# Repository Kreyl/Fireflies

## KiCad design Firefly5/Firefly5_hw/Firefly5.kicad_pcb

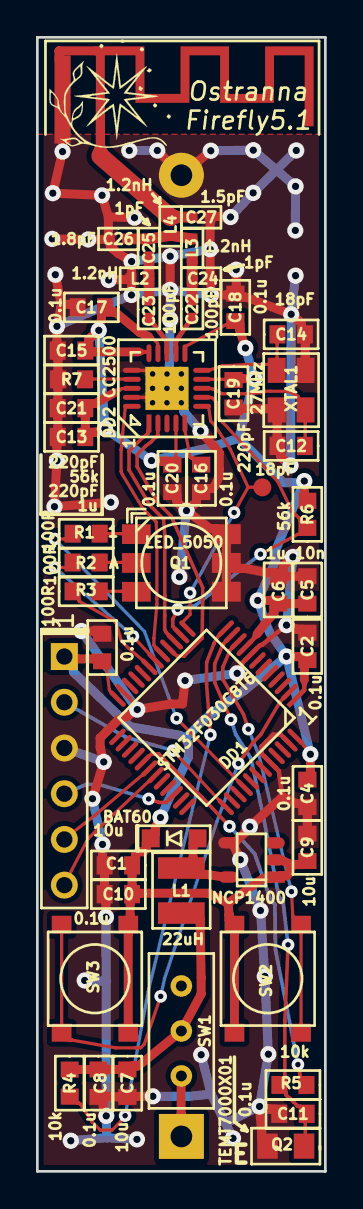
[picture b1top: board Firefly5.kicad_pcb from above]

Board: 2 copper layers, 16.0 x 63.0 mm, 53 parts (1 on the bottom side), 35 nets.

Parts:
ANT1: ANT_GENERAL; ANT_2400_MEANDER_MIRR
B1: BAT; BATTERY_AA
C1, C7, C9: 10u; CAP_0603
C2, C3, C4, C8, C10, C11, C16, C17, C18, C20: 0.1u; CAP_0603
C5: 10n; CAP_0603
C6, C13: 1u; CAP_0603
C12, C14: 18pF; CAP_0603
C15, C19, C21: 220pF; CAP_0603
C22, C23: 100pF; CAP_0402
C24, C25: 1pF; CAP_0402
C26: 1.8pF; CAP_0402
C27: 1.5pF; CAP_0402
D1: BAT60; SOD323
DA1: NCP1400; SOT23-5
DD1: STM32F030C8T6; LQFP48
DD2: CC2500; QFN20
L1: 22uH; IND_1210_LQH32C
L2, L3, L4: 1.2nH; IND_0402
Logo1: Logo; Ostranna_8x8
Q1: LED_5050
Q2: TEMT7000X01; RES_0805
R1, R2, R3: 100R; RES_0603
R4, R5: 10k; RES_0603
R6, R7: 56k; RES_0603
SW1: SWITCH; SW_SS-1P2T
SW2, SW3: Btn4x4; BTN_4x4_SMD
TP1: TESTPOINT; TESTPOINT_1MM
XL1: CONN_6; PLS-6
XTAL1: 27MHz; 03225C4

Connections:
+3.3V: C1.1, C2.1, C3.1, C4.1, C5.1, C6.1, C9.1, C10.1, C13.1, C15.1, C17.1, C18.1, C19.1, C20.1, C21.1, D1.C, DA1.1, DA1.2, DD1.1, DD1.9, DD1.24, DD1.48, DD2.4, DD2.9, DD2.11, DD2.14, DD2.15, DD2.18, R6.2, SW2.1, SW3.1, XL1.1
+BATT: C7.1, C8.1, L1.2, R4.1, SW1.2
/BAT_IN: B1.A, SW1.1
/BLUE_LED: DD1.40, R1.1
/BTN1: DD1.10, SW2.2
/BTN2: DD1.2, SW3.2
/CC_CS: DD1.14, DD2.7, R6.1
/CC_GDO0: DD1.13, DD2.6, TP1.1
/CC_MISO: DD1.16, DD2.2
/CC_MOSI: DD1.17, DD2.20
/CC_SCK: DD1.15, DD2.1
/GREEN_LED: DD1.19, R3.1
/LUM_MEAS: C11.1, DD1.11, Q2.1, R5.2
/Lout: D1.A, DA1.5, L1.1
/RED_LED: DD1.18, R2.1
/SWCLK: DD1.37, XL1.2
/SWDIO: DD1.34, XL1.4
/UART_RX: DD1.31, XL1.6
/UART_TX: DD1.30, XL1.5
GND: ANT1.2, B1.C, C1.2, C2.2, C3.2, C4.2, C5.2, C6.2, C7.2, C8.2, C9.2, C10.2, C11.2, C12.2, C13.2, C14.2, C15.2, C16.1, C17.2, C18.2, C19.2, C20.2, C21.2, C24.1, C26.1, C27.1, DA1.4, DD1.8, DD1.23, DD1.44, DD1.47, DD2.16, DD2.19, DD2.PAD, L2.2, Q1.4, Q1.5, Q1.6, Q2.2, R7.2, XL1.3, XTAL1.H
unnamed: ANT1.1, C27.2, L4.1
unnamed: C12.1, DD2.8, XTAL1.1
unnamed: C14.1, DD2.10, XTAL1.2
unnamed: C16.2, DD2.5
unnamed: C22.1, DD2.12
unnamed: C22.2, C24.2, L3.2
unnamed: C23.1, DD2.13
unnamed: C23.2, C25.1, L2.1
unnamed: C25.2, C26.2, L3.1, L4.2
unnamed: DD1.12, R4.2
unnamed: DD1.29, R5.1
unnamed: DD2.17, R7.1
unnamed: Q1.1, R1.2
unnamed: Q1.2, R2.2
unnamed: Q1.3, R3.2

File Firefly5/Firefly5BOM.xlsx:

Reference | Value | Footprint | Quantity | PN | SolderPointsDIP | Price | SolderPoints | URL | Sum
ANT1 | ANT_GENERAL | Radio:ANT_2400_MEANDER_MIRR | 1
B1 | BAT | Installation:BATTERY_AA | 1
C1 C7 C9 | 10u | Capacitors:CAP_0603 | 3 | CL10A106MQ8NNNC |  | 2.5 | 2 | https://www.terraelectronica.ru/catalog.php?ID=1155&search=c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
C12 C14 | 18pF | Capacitors:CAP_0603 | 2 |  |  | 0.5 | 2
C15 C19 C21 | 220pF | Capacitors:CAP_0603 | 3
C22 C23 | 100pF | Capacitors:CAP_0402 | 2 |  |  | 0.5 | 2
C24 C25 | 1pF | Capacitors:CAP_0402 | 2 |  |  | 0.5 | 2
C26 | 1.8pF | Capacitors:CAP_0402 | 1 |  |  | 0.5 | 2
C27 | 1.5pF | Capacitors:CAP_0402 | 1 |  |  | 0.5 | 2
C10 C11 C16 C17 C18 C2 C20 C3 C4 C8 | 0.1u | Capacitors:CAP_0603 | 10
C5 | 10n | Capacitors:CAP_0603 | 1
C13 C6 | 1u | Capacitors:CAP_0603 | 2
D1 | BAT60 | Diodes:SOD323 | 1 | BAT60JFILM |  | 5 | 2
DA1 | NCP1400 | SOT:SOT23-5 | 1 | NCP1400ASN33T1G |  | 7 | 5
DD1 | STM32F030C8Tx | LQFP_TQFP:LQFP48 | 1
DD2 | CC2500 | QFN_DFN:QFN20 | 1
L1 | 22uH | Inductors:IND_1210_LQH32C | 1 |  |  | 4 | 2
L2 L3 L4 | 1.2nH | Inductors:IND_0402 | 3 |  |  | 4 | 2
Logo1 | Logo | Pictures:Ostranna_8x8 | 1
Q1 | LED_5050 | LEDs:LED_5050 | 1 |  |  | 7 | 6
Q2 | TEMT7000X01 | Resistors:RES_0805 | 1 | TEMT7000X01
R1 R2 R3 | 100R | Resistors:RES_0603 | 3 |  |  | 0.5 | 2
R4 R5 | 10k | Resistors:RES_0603 | 2 |  |  | 0.5 | 2
R6 R7 | 56k | Resistors:RES_0603 | 2 |  |  | 0.5 | 2
SW1 | SWITCH | BtnsSwitches:SW_SS-1P2T | 1 |  |  | 5 | 5
SW2 SW3 | Btn4x4 | BtnsSwitches:BTN_4x4_SMD | 2 | IT-1187U |  | 1 | 4
TP1 | TESTPOINT | PCB:TESTPOINT_1MM | 1 |  |  | 0 | 0
XL1 | CONN_6 | Connectors:PLS-6 | 1 |  | 6
XTAL1 | 27MHz | Quartz:03225C4 | 1 |  |  | 15 | 4

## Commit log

2017-08-25 Start of Firefly5
2017-08-25 Sch nearly done
2017-08-25 Layout done
2017-08-26 Firefly5 ready for production
2017-09-05 + Firefly5 OS works
2017-09-05 * Switch systick to TIM14 + LED
2017-09-05 + btns
2017-09-05 + CC2500 init ok
2017-09-06 + Radio transmission ok
2018-03-13 * Something in FF3 + FF5.1
2018-03-27 Firefly 5.1 sent to factory
2018-04-05 Proceeding with Flash Save
2018-04-05 + Save/Load ID
2018-04-09 AlienTx RC
2018-04-09 Radio works
2018-04-12 Release
